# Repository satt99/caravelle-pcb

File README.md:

# caravelle-pcb
PCB for caravelle keyboard

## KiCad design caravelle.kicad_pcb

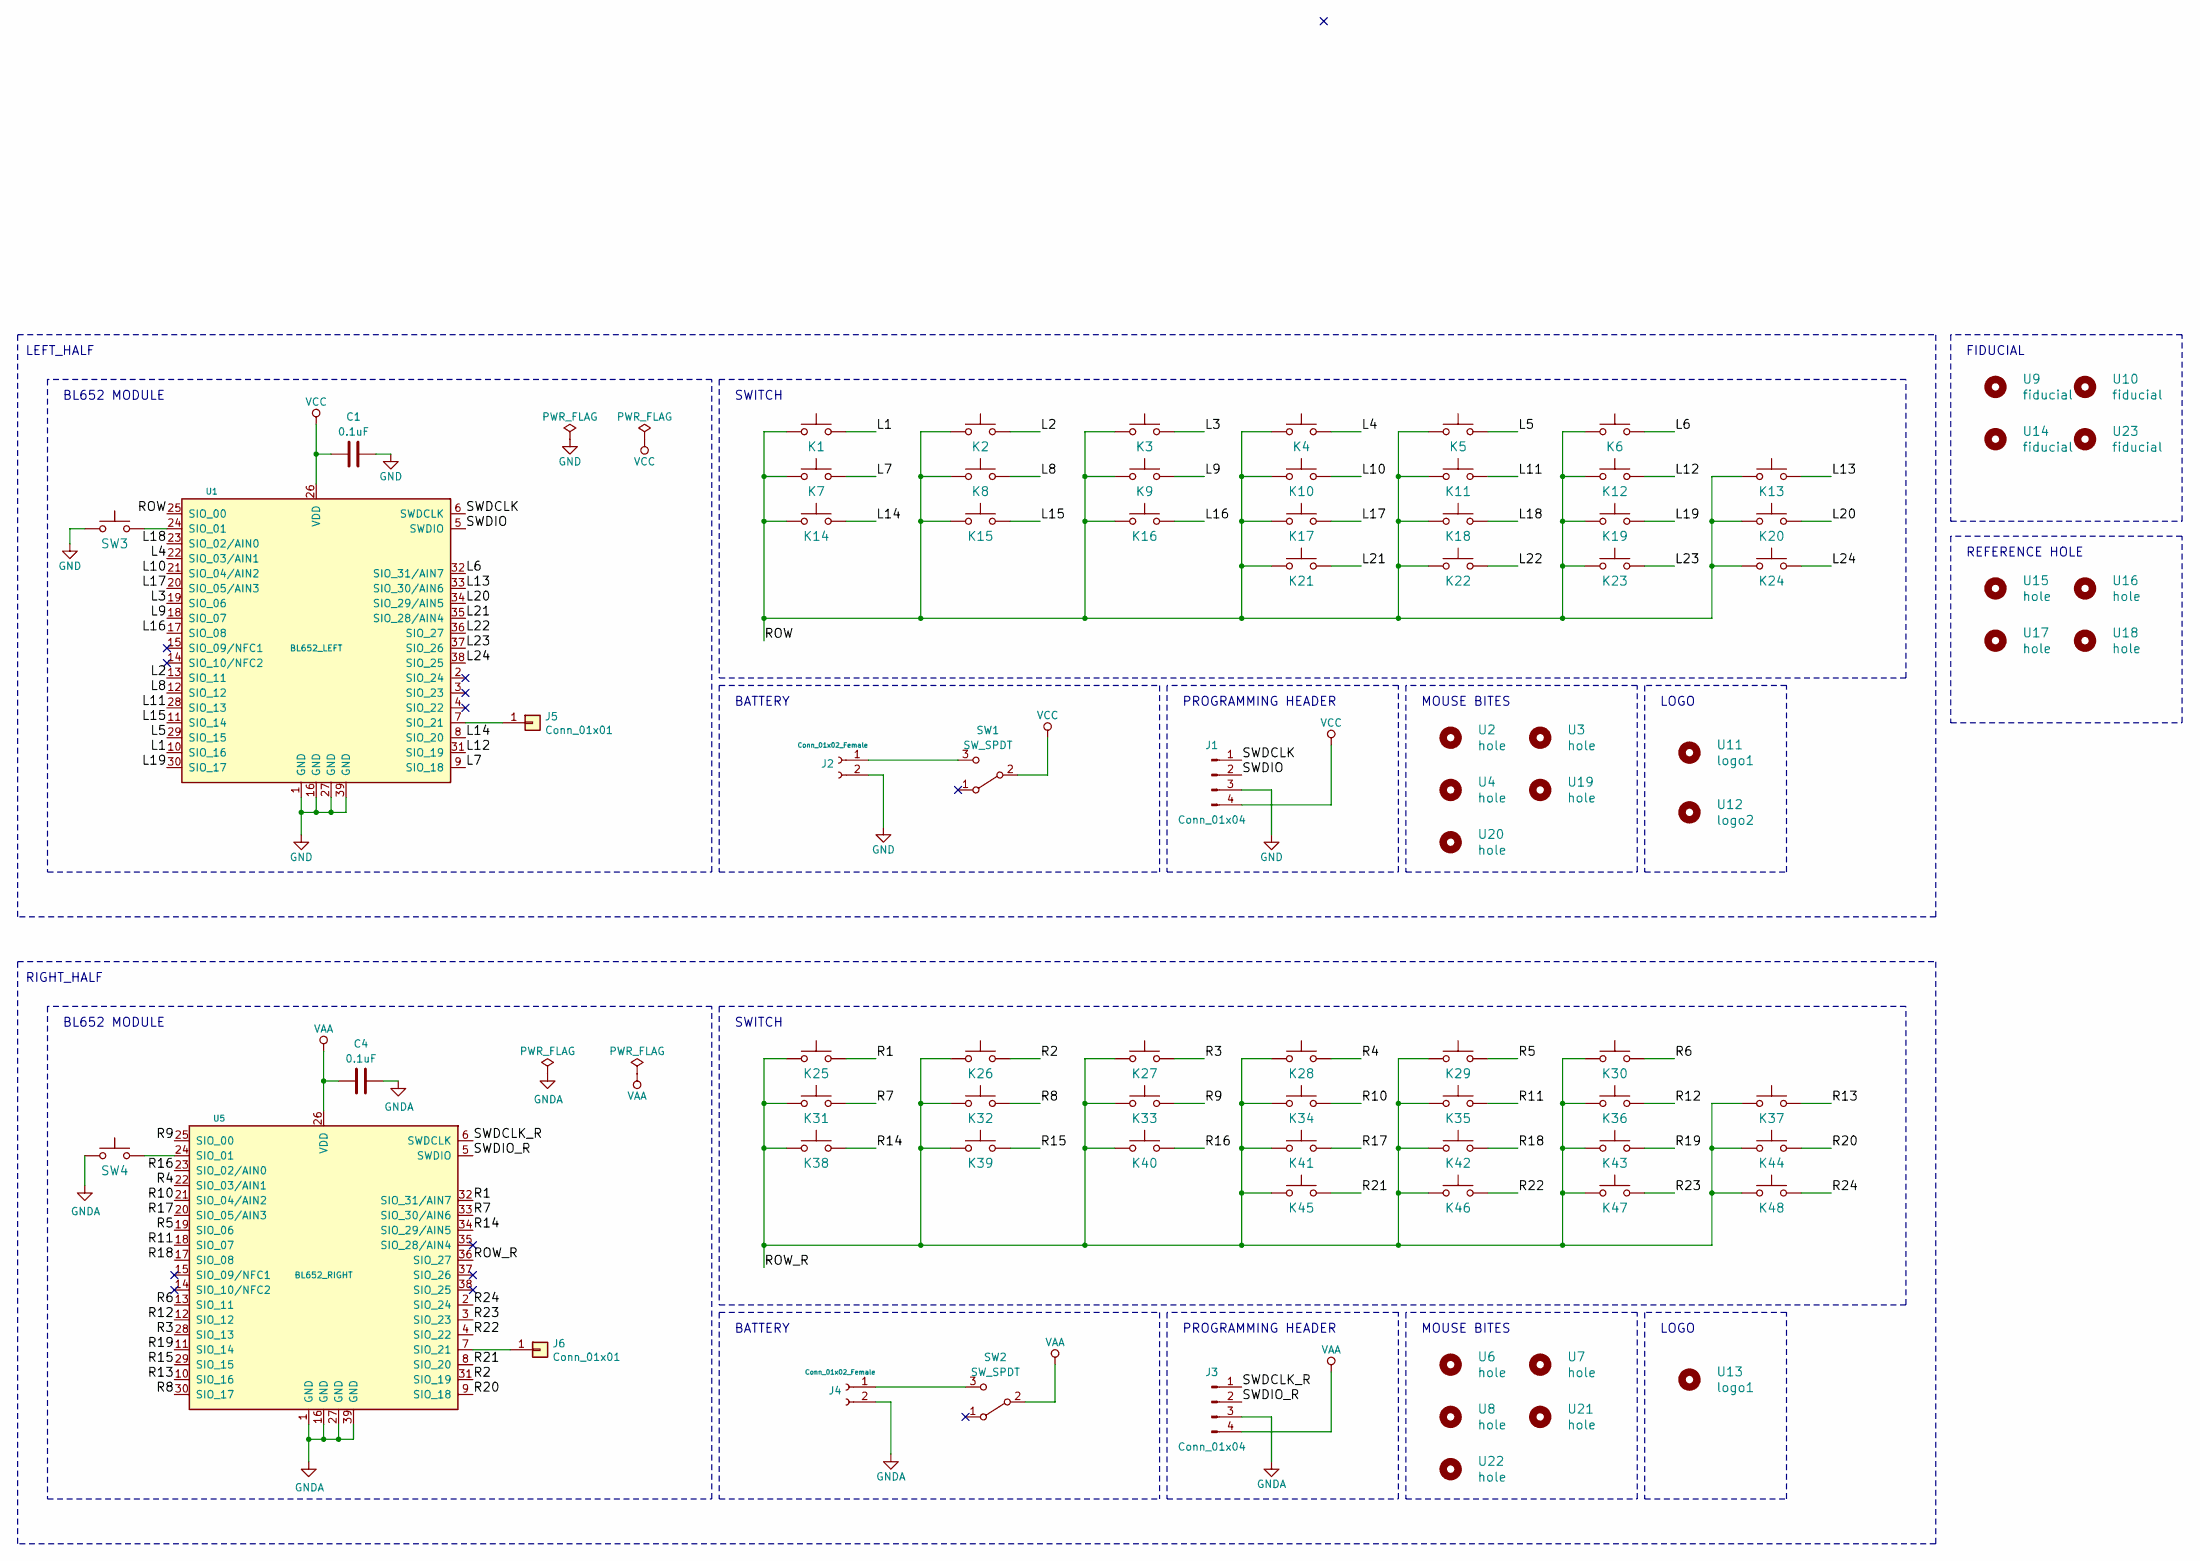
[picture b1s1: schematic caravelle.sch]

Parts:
C1, C4: 0.1uF; C_0603_1608Metric_Pad1.05x0.95mm_HandSolder
J1, J3: Conn_01x04; programming_port
J2, J4: Conn_01x02_Female; JST_PH_S2B-PH-K_1x02_P2.00mm_Horizontal
J5, J6: Conn_01x01; breakout-pad
K1, K2, K3, K4, K5, K6, K7, K8, K9, K10, K11, K12, K13, K14, K15, K16, K17, K18, K19, K20, K21, K22, K23, K24, K25, K26, K27, K28, K29, K30, K31, K32, K33, K34, K35, K36, K37, K38, K39, K40, K41, K42, K43, K44, K45, K46, K47, K48: keyboard_parts_KEYSW; MXOnly-1U-Hotswap-Antishear
SW1, SW2: SW_SPDT; slide_switch_vertical_01x03_pitch2mm
SW3, SW4: RESET_SW; SW_SPST_ALPS-SKRP
U1: BL652_LEFT; Laird_BL652
U2, U3, U4, U6, U7, U8, U19, U20, U21, U22: hole; breakaway-mousebites
U5: BL652_RIGHT; Laird_BL652
U9, U10: fiducial; Fiducial_1mm_Mask3mm
U11, U13: logo1
U12: logo2
U14, U23: fiducial; Fiducial_0.75mm_Mask2.25mm
U15, U16, U17, U18: hole; MountingHole_4mm

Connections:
/L1: K1.2, U1.10 (SIO_16)
/L2: K2.2, U1.13 (SIO_11)
/L3: K3.2, U1.19 (SIO_06)
/L4: K4.2, U1.22 (SIO_03/AIN1)
/L5: K5.2, U1.29 (SIO_15)
/L6: K6.2, U1.32 (SIO_31/AIN7)
/L7: K7.2, U1.9 (SIO_18)
/L8: K8.2, U1.12 (SIO_12)
/L9: K9.2, U1.18 (SIO_07)
/L10: K10.2, U1.21 (SIO_04/AIN2)
/L11: K11.2, U1.28 (SIO_13)
/L12: K12.2, U1.31 (SIO_19)
/L13: K13.2, U1.33 (SIO_30/AIN6)
/L14: K14.2, U1.8 (SIO_20)
/L15: K15.2, U1.11 (SIO_14)
/L16: K16.2, U1.17 (SIO_08)
/L17: K17.2, U1.20 (SIO_05/AIN3)
/L18: K18.2, U1.23 (SIO_02/AIN0)
/L19: K19.2, U1.30 (SIO_17)
/L20: K20.2, U1.34 (SIO_29/AIN5)
/L21: K21.2, U1.35 (SIO_28/AIN4)
/L22: K22.2, U1.36 (SIO_27)
/L23: K23.2, U1.37 (SIO_26)
/L24: K24.2, U1.38 (SIO_25)
/R1: K25.2, U5.32 (SIO_31/AIN7)
/R2: K26.2, U5.31 (SIO_19)
/R3: K27.2, U5.28 (SIO_13)
/R4: K28.2, U5.22 (SIO_03/AIN1)
/R5: K29.2, U5.19 (SIO_06)
/R6: K30.2, U5.13 (SIO_11)
/R7: K31.2, U5.33 (SIO_30/AIN6)
/R8: K32.2, U5.30 (SIO_17)
/R9: K33.2, U5.25 (SIO_00)
/R10: K34.2, U5.21 (SIO_04/AIN2)
/R11: K35.2, U5.18 (SIO_07)
/R12: K36.2, U5.12 (SIO_12)
/R13: K37.2, U5.10 (SIO_16)
/R14: K38.2, U5.34 (SIO_29/AIN5)
/R15: K39.2, U5.29 (SIO_15)
/R16: K40.2, U5.23 (SIO_02/AIN0)
/R17: K41.2, U5.20 (SIO_05/AIN3)
/R18: K42.2, U5.17 (SIO_08)
/R19: K43.2, U5.11 (SIO_14)
/R20: K44.2, U5.9 (SIO_18)
/R21: K45.2, U5.8 (SIO_20)
/R22: K46.2, U5.4 (SIO_22)
/R23: K47.2, U5.3 (SIO_23)
/R24: K48.2, U5.2 (SIO_24)
/ROW: K1.1, K2.1, K3.1, K4.1, K5.1, K6.1, K7.1, K8.1, K9.1, K10.1, K11.1, K12.1, K13.1, K14.1, K15.1, K16.1, K17.1, K18.1, K19.1, K20.1, K21.1, K22.1, K23.1, K24.1, U1.25 (SIO_00)
/ROW_R: K25.1, K26.1, K27.1, K28.1, K29.1, K30.1, K31.1, K32.1, K33.1, K34.1, K35.1, K36.1, K37.1, K38.1, K39.1, K40.1, K41.1, K42.1, K43.1, K44.1, K45.1, K46.1, K47.1, K48.1, U5.36 (SIO_27)
/SWDCLK: J1.1, U1.6 (SWDCLK)
/SWDCLK_R: J3.1, U5.6 (SWDCLK)
/SWDIO: J1.2, U1.5 (SWDIO)
/SWDIO_R: J3.2, U5.5 (SWDIO)
GND: C1.2, J1.3, J2.2, SW3.1, U1.1 (GND), U1.16 (GND), U1.27 (GND), U1.39 (GND)
GNDA: C4.2, J3.3, J4.2, SW4.1, U5.1 (GND), U5.16 (GND), U5.27 (GND), U5.39 (GND)
unnamed: J2.1, SW1.3 (C)
unnamed: J4.1, SW2.3 (C)
unnamed: J5.1, U1.7 (SIO_21)
unnamed: J6.1, U5.7 (SIO_21)
unnamed: SW3.2, U1.24 (SIO_01)
unnamed: SW4.2, U5.24 (SIO_01)
VAA: C4.1, J3.4, SW2.2 (B), U5.26 (VDD)
VCC: C1.1, J1.4, SW1.2 (B), U1.26 (VDD)

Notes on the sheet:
LEFT_HALF
BL652 MODULE
SWITCH
RIGHT_HALF
MOUSE BITES
PROGRAMMING HEADER
BATTERY
LOGO
FIDUCIAL
REFERENCE HOLE

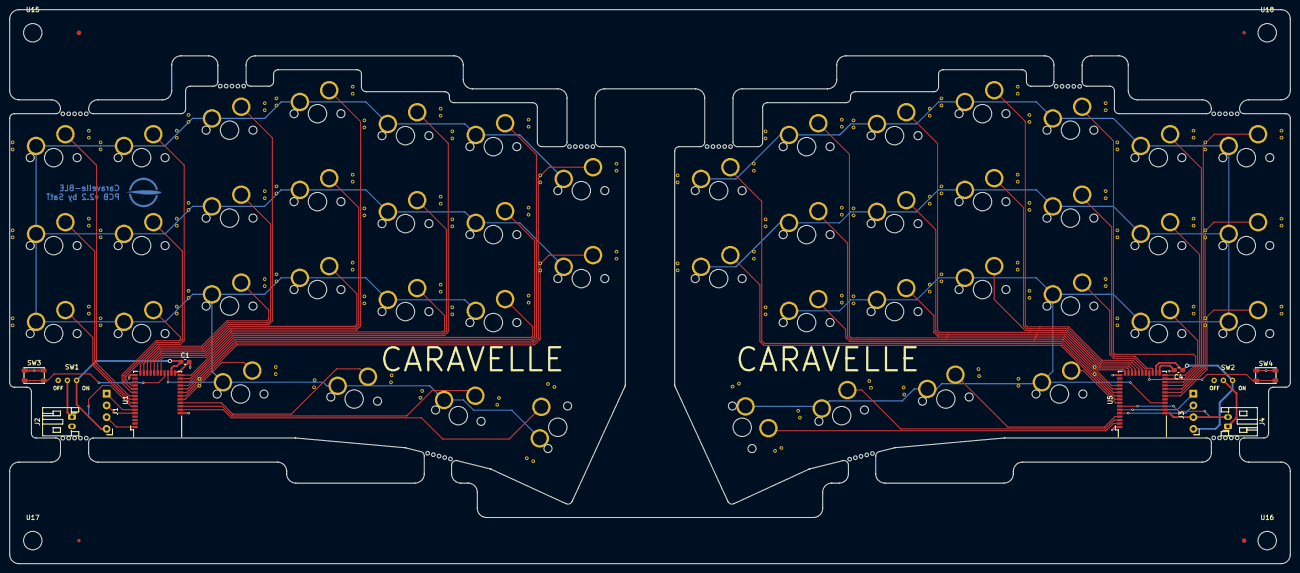
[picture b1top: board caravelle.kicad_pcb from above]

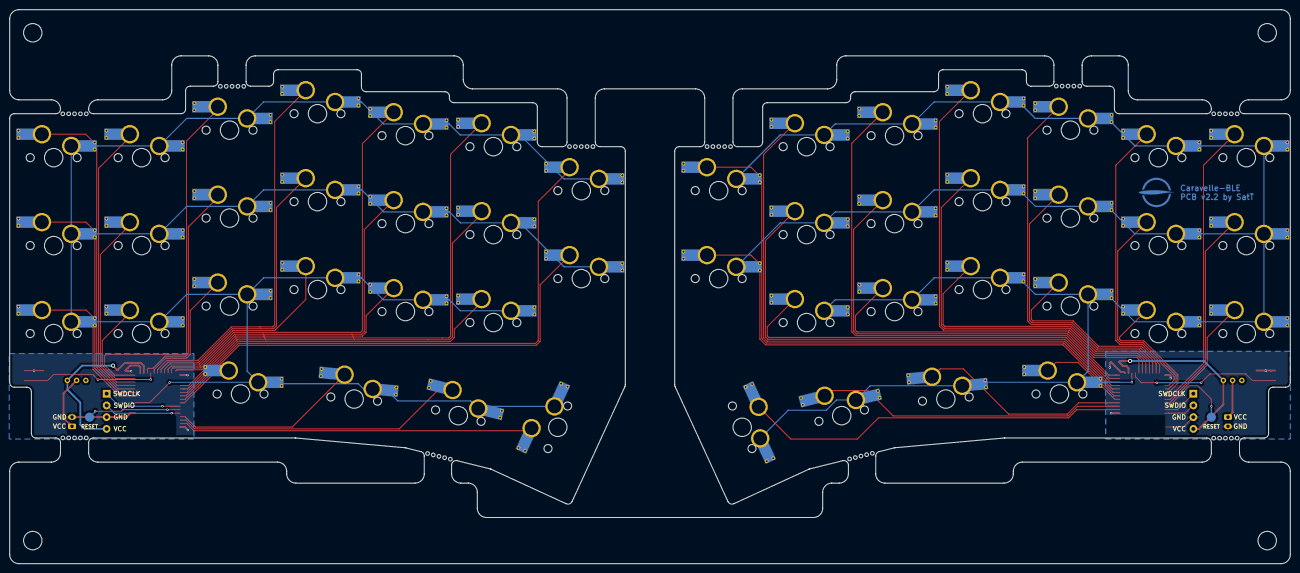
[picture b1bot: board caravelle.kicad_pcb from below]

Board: 2 copper layers, 277.4 x 120.0 mm, 83 parts (3 on the bottom side), 64 nets.

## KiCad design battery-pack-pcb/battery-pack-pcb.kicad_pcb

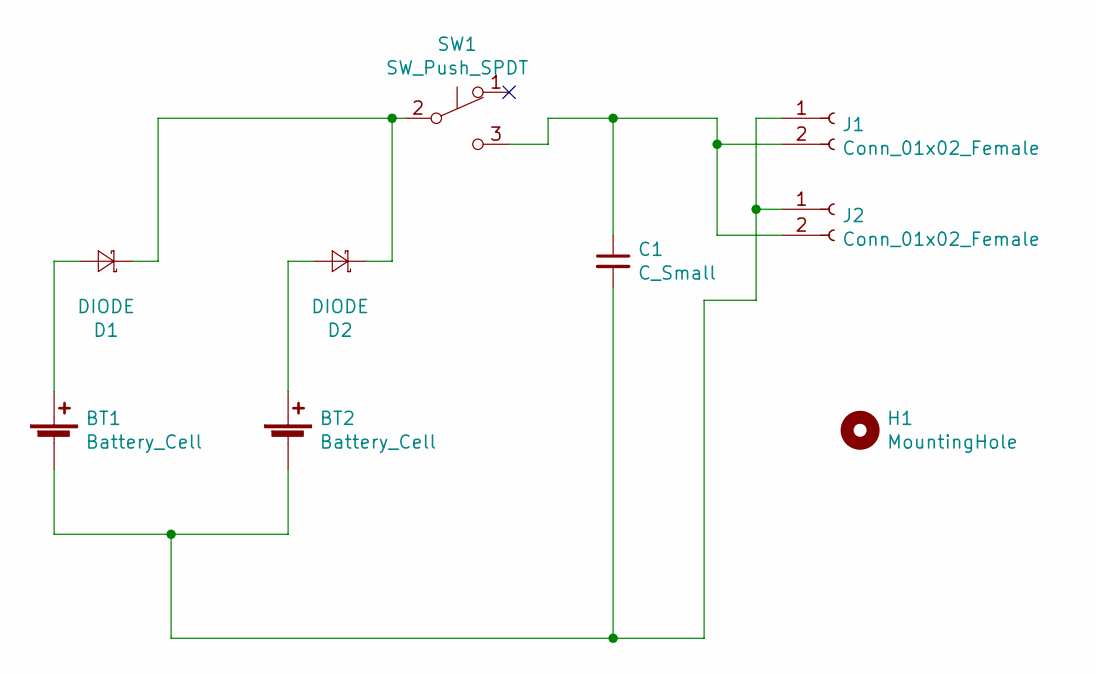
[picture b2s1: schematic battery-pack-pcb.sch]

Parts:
BT1, BT2: Battery_Cell; CR2032_BAT-HLD
C1: C_Small; C_1210_3225Metric_Pad1.42x2.65mm_HandSolder
D1, D2: DIODE; D_SOD-123
H1: MountingHole; MountingHole_2.2mm_M2
J1, J2: Conn_01x02_Female; JST_PH_S2B-PH-K_1x02_P2.00mm_Horizontal_nosilk
SW1: SW_Push_SPDT; slide_switch_vertical_01x03_pitch2mm

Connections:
unnamed: BT1.1 (+), D1.2 (A)
unnamed: BT1.2 (-), BT2.2 (-), C1.2, J1.1, J2.1
unnamed: BT2.1 (+), D2.2 (A)
unnamed: C1.1, J1.2, J2.2, SW1.3 (C)
unnamed: D1.1 (K), D2.1 (K), SW1.2 (B)

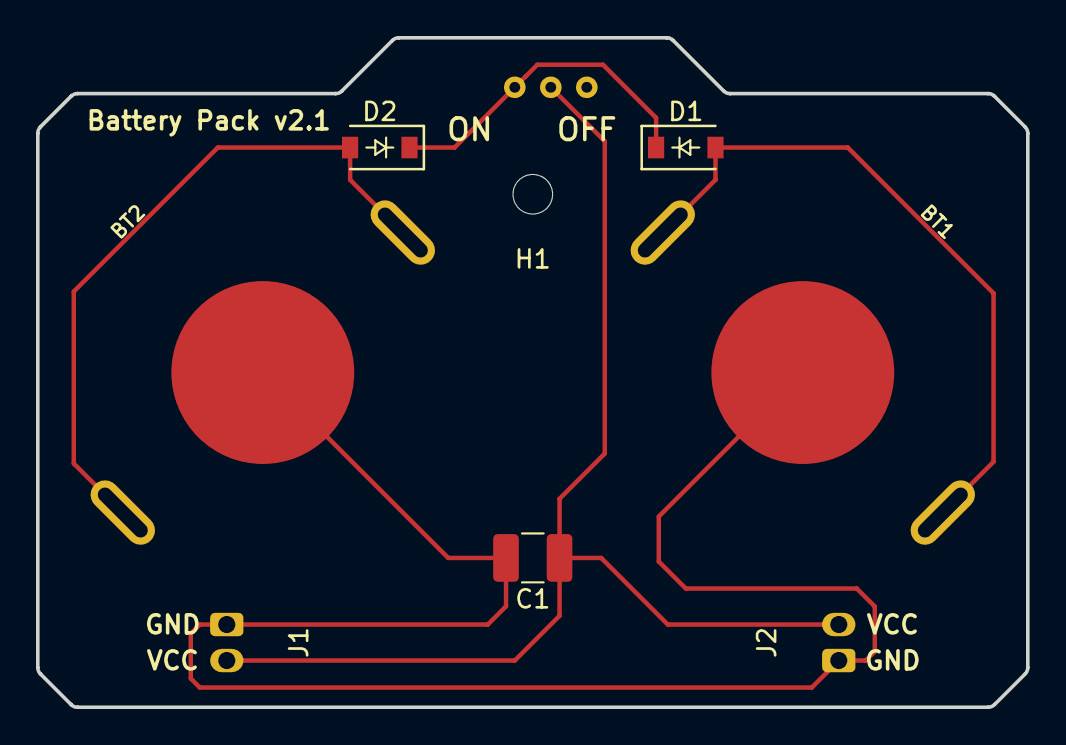
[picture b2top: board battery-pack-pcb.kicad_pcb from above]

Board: 2 copper layers, 55.0 x 37.2 mm, 9 parts (1 on the bottom side), 5 nets.

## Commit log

2019-08-26 Add submodules
2019-08-26 Add v1.5 PCB
2019-08-26 Add v2.0 PCB
2019-08-27 Minor fix to routing
2019-10-05 Add v1.0 battery pack PCB
2019-10-05 Add capacitor to battery pack
2019-10-06 Add DFU button
2019-10-06 Add breakout pad for reset
2019-10-06 Change matrix wiring
2019-10-19 Fix capacitor location & refine wiring
2019-10-20 Change logo from silk to mask
2019-10-20 Update silk of battery pack pcb
2019-10-21 Add PCB plate
2019-10-21 Update PCB plate
2019-11-16 Add power switch to battery PCB
2019-12-22 Add edge rails for PCBA
2019-12-22 Clean up Fab
2020-01-04 Furthermore cleanup
2020-01-04 Adjust silk & hole size of battery pack
2020-01-04 Add Kailh hotswap footprint
2020-07-05 Update switch cutout size of PCB plate
